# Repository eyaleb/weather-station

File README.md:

# weather-station
A collaborative project at MHV

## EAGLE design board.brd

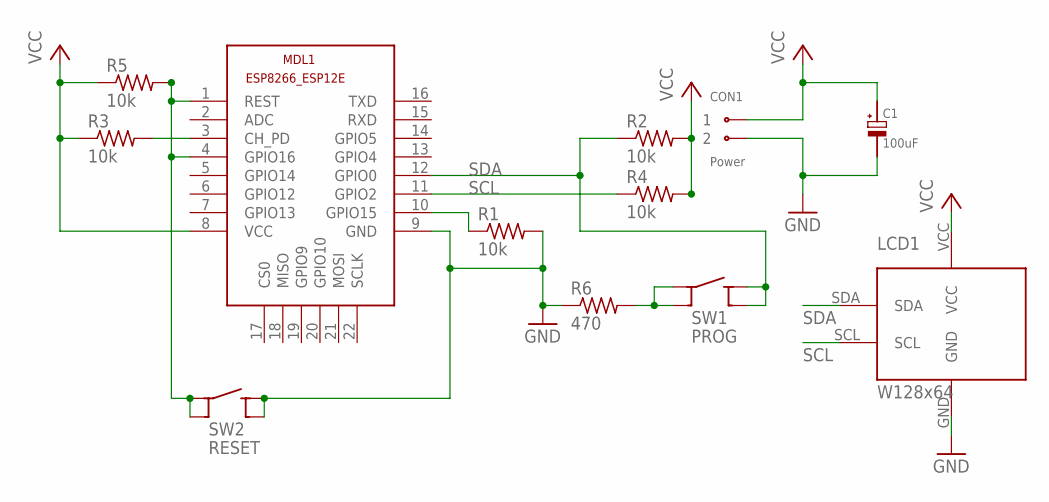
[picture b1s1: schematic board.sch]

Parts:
C1: 100uF; POLTANT02
CON1: Power; CON-WEID-PCB2
LCD1: W128x64; OLED_SMALL_I2C
MDL1: ESP8266; ESP8266-ESP12E
R1, R2, R3, R4, R5: 10k; R0805
R6: 470; R0805
SW1: PROG; SWITCH-SPST-MOMENTARY
SW2: RESET; SWITCH-SPST-MOMENTARY

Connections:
GND: C1.MINUS (NEGATIVE), CON1.2, LCD1.GND, MDL1.9 (GND), R1.2, R6.1, SW2.P$3, SW2.P$4
unnamed: MDL1.10 (GPIO15), R1.1
unnamed: MDL1.3 (CH_PD), R3.2
unnamed: MDL1.1 (REST), MDL1.4 (GPIO16), R5.2, SW2.P$1, SW2.P$2
unnamed: R6.2, SW1.P$1, SW1.P$2
SCL: LCD1.SCL, MDL1.11 (GPIO2), R4.1
SDA: LCD1.SDA, MDL1.12 (GPIO0), R2.1, SW1.P$3, SW1.P$4
VCC: C1.PLUS (POSITIVE), CON1.1, LCD1.VCC, MDL1.8 (VCC), R2.2, R3.1, R4.2, R5.1

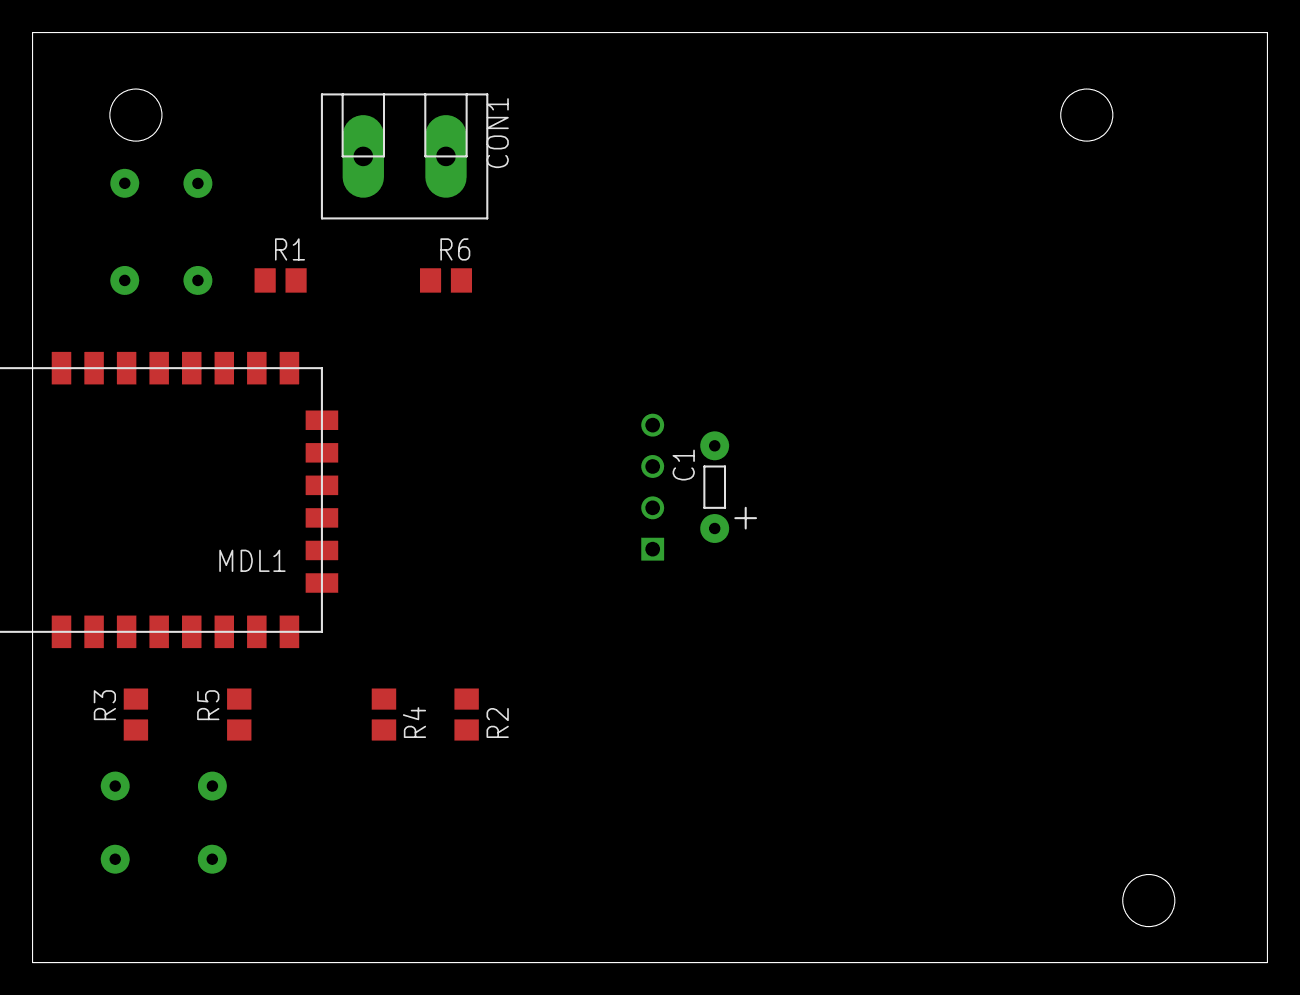
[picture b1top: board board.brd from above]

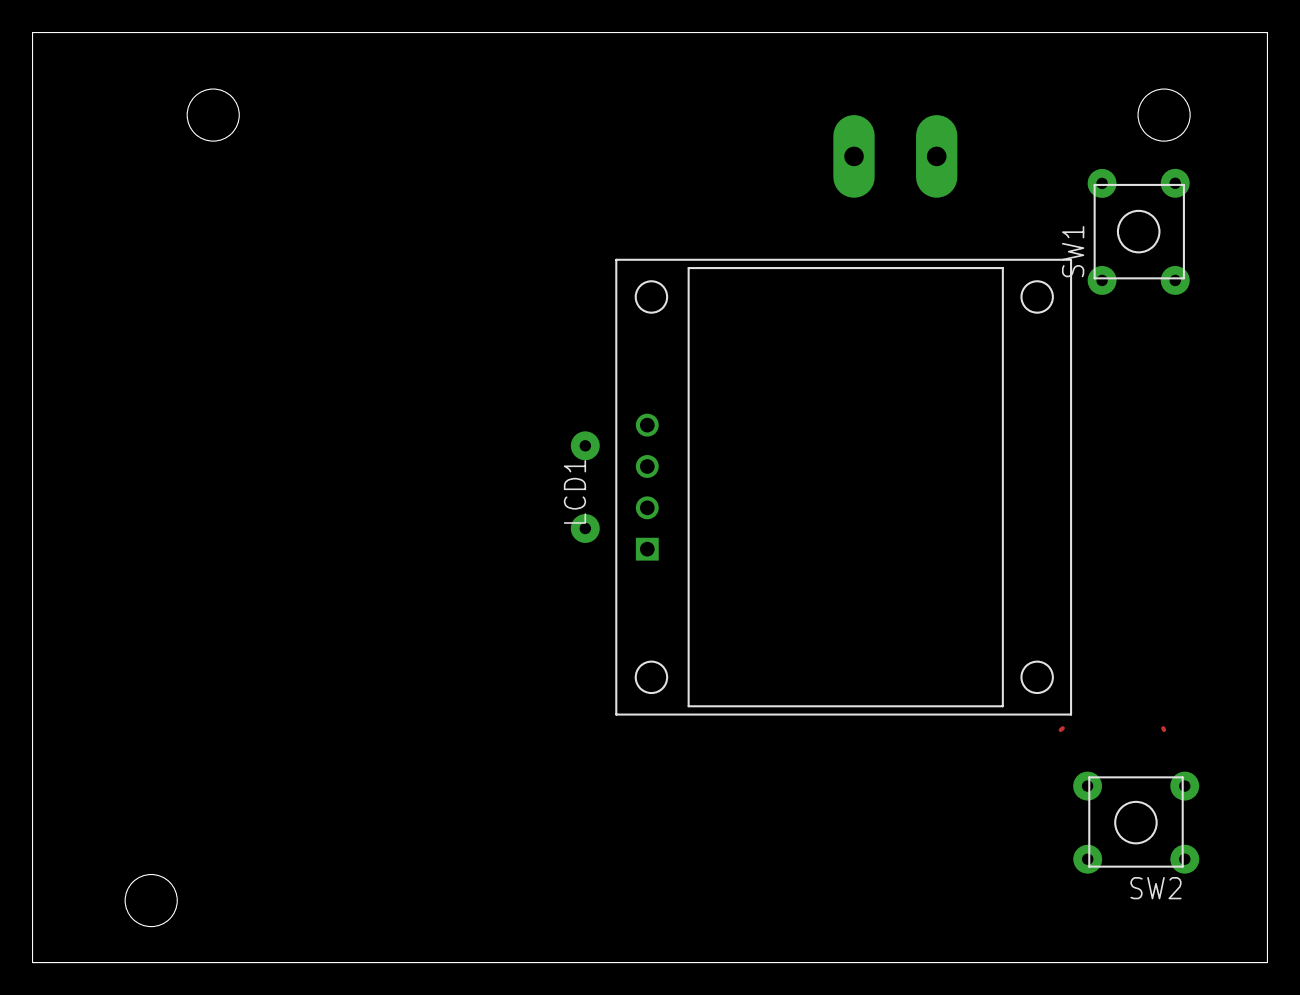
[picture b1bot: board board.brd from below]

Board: 2 copper layers, 75.9 x 57.1 mm, 12 parts (3 on the bottom side), 8 nets.

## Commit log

2016-08-31 Start new project
    Just learning to set up the repo
2016-10-19 Add files via upload
    Started creating the board
2016-10-19 Add files via upload
    Sharing Steve's libraries
2016-10-28 Modifications last MHV meeting.
